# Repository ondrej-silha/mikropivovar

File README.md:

Mikropivovar
=
Homemade microbrewery control system with the possibility of controlling the cellar and the pump.
Powered by Atmega328PU

Futures
-
* 4 relay output (3x AC 230, 1x DC 12V)
* 2 temperature input
* Graphic color touchable display
* Beeper

Used software
- 
* Kicad
* Freecad
* Arduino ide
* Nextion editor

Board preview
-

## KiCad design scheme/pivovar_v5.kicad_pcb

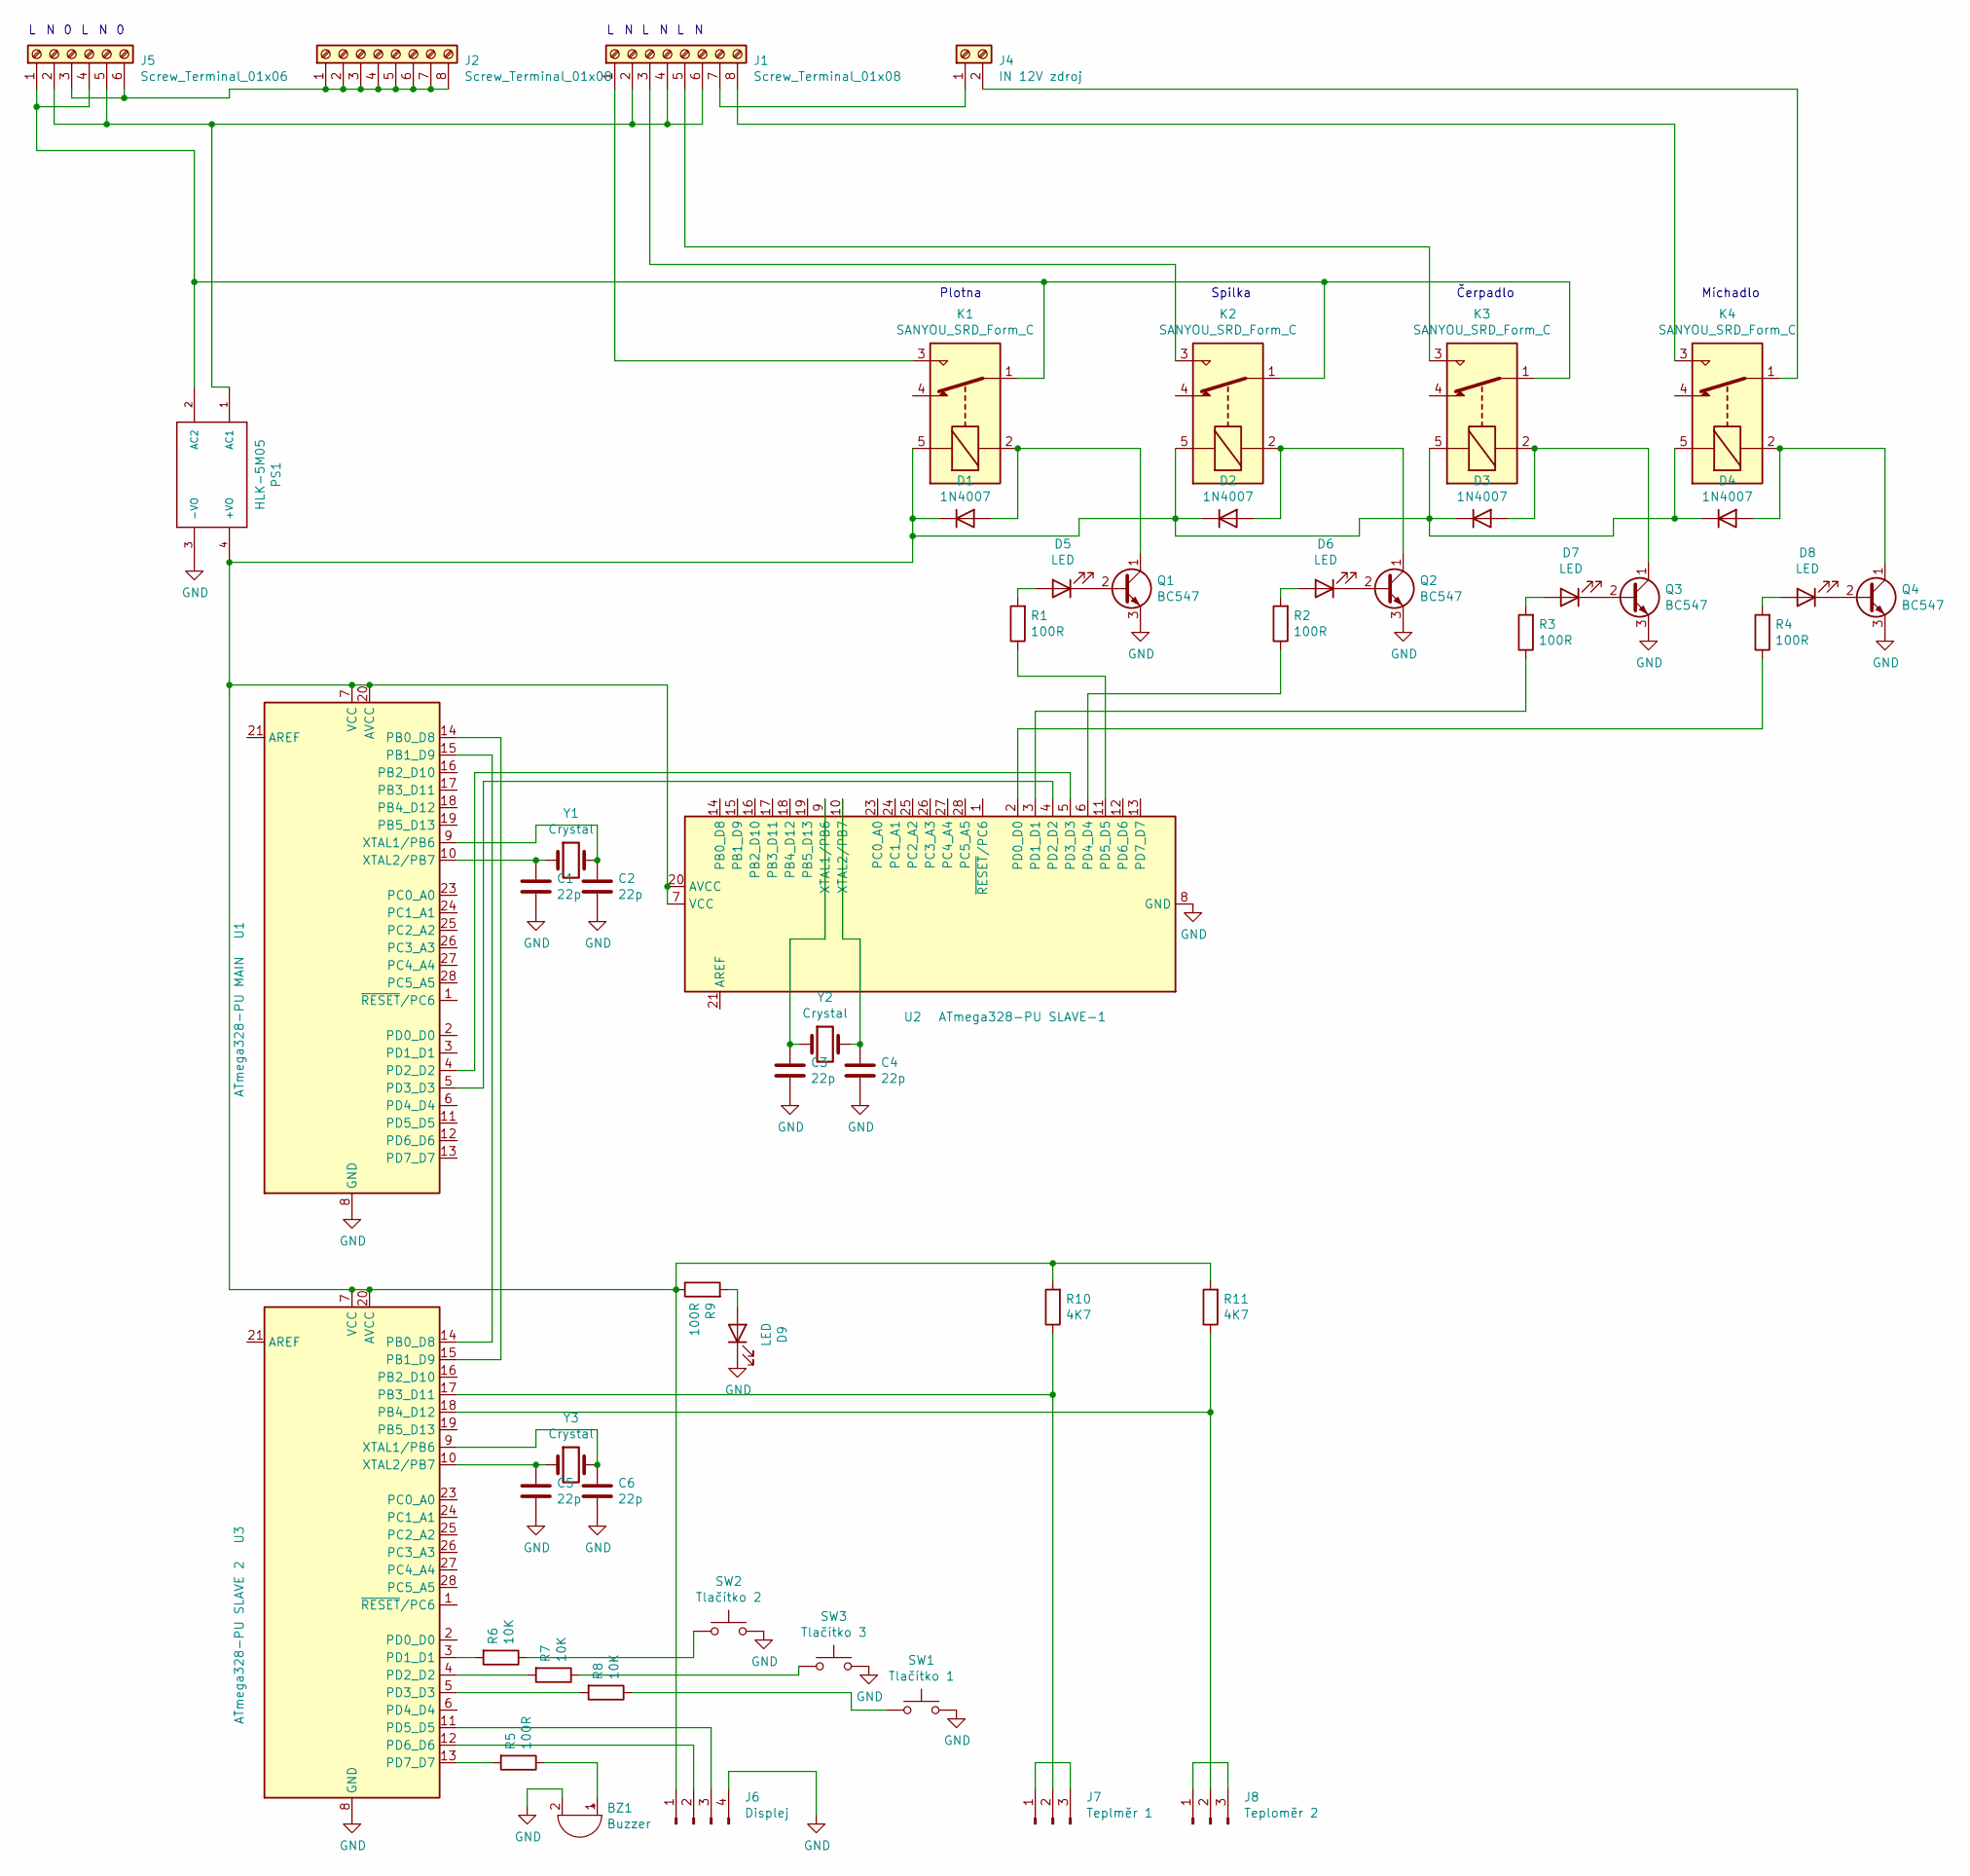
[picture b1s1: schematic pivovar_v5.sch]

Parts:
BZ1: Buzzer; JST_EH_B2B-EH-A_1x02_P2.50mm_Vertical
C1, C2, C3, C4, C5, C6: 22p; C_Disc_D6.0mm_W4.4mm_P5.00mm
D1, D2, D3, D4: 1N4007; D_DO-15_P12.70mm_Horizontal
D5, D6, D7, D8, D9: LED; JST_EH_B2B-EH-A_1x02_P2.50mm_Vertical
J1, J2: Screw_Terminal_01x08; TerminalBlock_Phoenix_MKDS-1,5-8-5.08_1x08_P5.08mm_Horizont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
J4: IN 12V zdroj; TerminalBlock_Phoenix_MKDS-1,5-2-5.08_1x02_P5.08mm_Horizont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
J5: Screw_Terminal_01x06; TerminalBlock_Phoenix_MKDS-1,5-6-5.08_1x06_P5.08mm_Horizont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
J6: Displej; JST_EH_B4B-EH-A_1x04_P2.50mm_Vertical
J7: Teplměr 1; JST_EH_B3B-EH-A_1x03_P2.50mm_Vertical
J8: Teploměr 2; JST_EH_B3B-EH-A_1x03_P2.50mm_Vertical
K1, K2, K3, K4: SANYOU_SRD_Form_C; Relay_SPDT_SANYOU_SRD_Series_Form_C
PS1: HLK-5M05; CONV_HLK-5M05
Q1, Q2, Q3, Q4: BC547; TO-92_Inline_Wide
R1, R2, R3, R4, R5, R9: 100R; R_Axial_DIN0309_L9.0mm_D3.2mm_P12.70mm_Horizontal
R6, R7, R8: 10K; R_Axial_DIN0309_L9.0mm_D3.2mm_P12.70mm_Horizontal
R10, R11: 4K7; R_Axial_DIN0309_L9.0mm_D3.2mm_P12.70mm_Horizontal
SW1: Tlačítko 1; JST_EH_B2B-EH-A_1x02_P2.50mm_Vertical
SW2: Tlačítko 2; JST_EH_B2B-EH-A_1x02_P2.50mm_Vertical
SW3: Tlačítko 3; JST_EH_B2B-EH-A_1x02_P2.50mm_Vertical
U1: ATmega328-PU MAIN; DIP-28_W7.62mm
U2: ATmega328-PU SLAVE-1; DIP-28_W7.62mm
U3: ATmega328-PU SLAVE 2; DIP-28_W7.62mm
Y1, Y2, Y3: Crystal; Crystal_HC49-4H_Vertical

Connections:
GND: BZ1.2 (+), C1.2, C2.2, C3.2, C4.2, C5.2, C6.2, D9.1 (K), J6.4, PS1.3 (-VO), Q1.3 (E), Q2.3 (E), Q3.3 (E), Q4.3 (E), SW1.2, SW2.2, SW3.2, U1.8 (GND), U1.22 (GND), U2.8 (GND), U2.22 (GND), U3.8 (GND), U3.22 (GND); also elsewhere on the board
unnamed: BZ1.1 (-), R5.1
unnamed 2: C1.1, U1.10 (XTAL2/PB7), Y1.1; also elsewhere on the board
unnamed 3: C2.1, U1.9 (XTAL1/PB6), Y1.2; also elsewhere on the board
unnamed 4: C3.1, U2.9 (XTAL1/PB6), Y2.1; also elsewhere on the board
unnamed 5: C4.1, U2.10 (XTAL2/PB7), Y2.2; also elsewhere on the board
unnamed 6: C5.1, U3.10 (XTAL2/PB7), Y3.1; also elsewhere on the board
unnamed 7: C6.1, U3.9 (XTAL1/PB6), Y3.2; also elsewhere on the board
unnamed 8: D1.1 (K), D2.1 (K), D3.1 (K), D4.1 (K), J6.1, K1.5, K2.5, K3.5, K4.5, PS1.4 (+VO), R9.1, R10.2, R11.2, U1.7 (VCC), U1.20 (AVCC), U2.7 (VCC), U2.20 (AVCC), U3.7 (VCC), U3.20 (AVCC); also elsewhere on the board
unnamed: D1.2 (A), K1.2, Q1.1 (C)
unnamed: D2.2 (A), K2.2, Q2.1 (C)
unnamed: D3.2 (A), K3.2, Q3.1 (C)
unnamed: D4.2 (A), K4.2, Q4.1 (C)
unnamed: D5.1 (K), Q1.2 (B)
unnamed: D5.2 (A), R1.2
unnamed: D6.1 (K), Q2.2 (B)
unnamed: D6.2 (A), R2.2
unnamed: D7.1 (K), Q3.2 (B)
unnamed: D7.2 (A), R3.2
unnamed: D8.1 (K), Q4.2 (B)
unnamed: D8.2 (A), R4.2
unnamed: D9.2 (A), R9.2
unnamed: J1.1, K1.3
unnamed: J1.2, J1.4, J1.6, J5.2, J5.5, PS1.1 (AC1)
unnamed: J1.3, K2.3
unnamed: J1.5, K3.3
unnamed: J1.7, J4.1
unnamed: J1.8, K4.3
unnamed: J2.1, J2.2, J2.3, J2.4, J2.5, J2.6, J2.7, J2.8, J5.3, J5.6
unnamed: J4.2, K4.1
unnamed: J5.1, J5.4, K1.1, K2.1, K3.1, PS1.2 (AC2)
unnamed 31: J6.2, U3.12 (PD6_D6); also elsewhere on the board
unnamed 32: J6.3, U3.11 (PD5_D5); also elsewhere on the board
unnamed: J7.1, J7.3
unnamed 34: J7.2, R10.1, U3.17 (PB3_D11); also elsewhere on the board
unnamed: J8.1, J8.3
unnamed 36: J8.2, R11.1, U3.18 (PB4_D12); also elsewhere on the board
unnamed 41: R1.1, U2.11 (PD5_D5); also elsewhere on the board
unnamed 42: R2.1, U2.6 (PD4_D4); also elsewhere on the board
unnamed 43: R3.1, U2.3 (PD1_D1); also elsewhere on the board
unnamed 44: R4.1, U2.2 (PD0_D0); also elsewhere on the board
unnamed 45: R5.2, U3.13 (PD7_D7); also elsewhere on the board
unnamed: R6.1, SW2.1
unnamed 47: R6.2, U3.3 (PD1_D1); also elsewhere on the board
unnamed: R7.1, SW3.1
unnamed 49: R7.2, U3.4 (PD2_D2); also elsewhere on the board
unnamed: R8.1, SW1.1
unnamed 51: R8.2, U3.5 (PD3_D3); also elsewhere on the board
unnamed 55: U1.4 (PD2_D2), U2.5 (PD3_D3); also elsewhere on the board
unnamed 56: U1.5 (PD3_D3), U2.4 (PD2_D2); also elsewhere on the board
unnamed 61: U1.14 (PB0_D8), U3.15 (PB1_D9); also elsewhere on the board
unnamed 62: U1.15 (PB1_D9), U3.14 (PB0_D8); also elsewhere on the board

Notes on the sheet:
Plotna
Spilka
Čerpadlo
Míchadlo

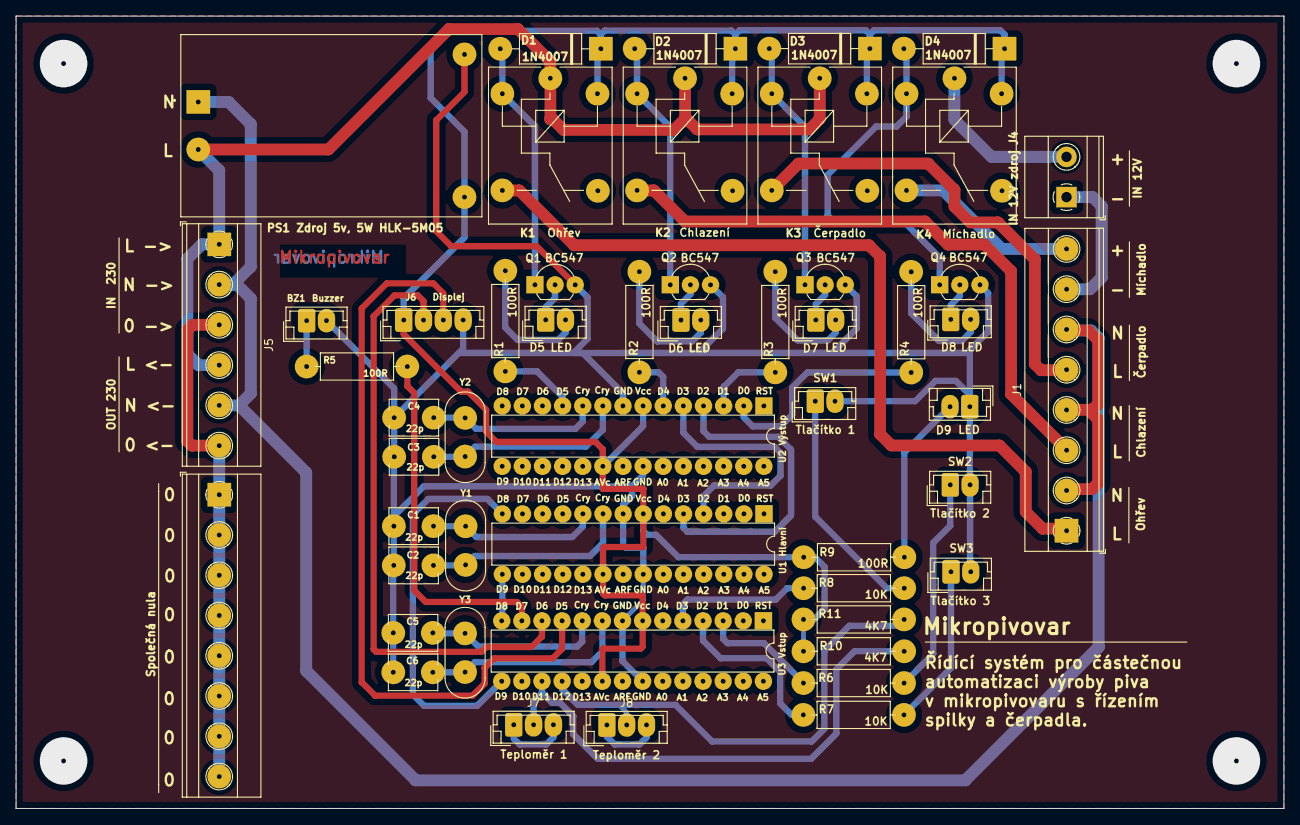
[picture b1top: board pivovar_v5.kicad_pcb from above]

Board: 2 copper layers, 160.0 x 100.0 mm, 52 parts (0 on the bottom side), 52 nets.

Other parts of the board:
U1 Hlavní: ATmega328-PU MAIN; DIP-28_W7.62mm
U2 Výstup: ATmega328-PU SLAVE-1; DIP-28_W7.62mm
U3 Vstup: ATmega328-PU SLAVE 2; DIP-28_W7.62mm

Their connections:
GND: U1 Hlavní.8, U1 Hlavní.22, U2 Výstup.8, U2 Výstup.22, U3 Vstup.8, U3 Vstup.22; also elsewhere on the board
unnamed 2: U1 Hlavní.10; also elsewhere on the board
unnamed 3: U1 Hlavní.9; also elsewhere on the board
unnamed 4: U2 Výstup.9; also elsewhere on the board
unnamed 5: U2 Výstup.10; also elsewhere on the board
unnamed 6: U3 Vstup.10; also elsewhere on the board
unnamed 7: U3 Vstup.9; also elsewhere on the board
unnamed 8: U1 Hlavní.7, U1 Hlavní.20, U2 Výstup.7, U2 Výstup.20, U3 Vstup.7, U3 Vstup.20; also elsewhere on the board
unnamed 31: U3 Vstup.12; also elsewhere on the board
unnamed 32: U3 Vstup.11; also elsewhere on the board
unnamed 34: U3 Vstup.17; also elsewhere on the board
unnamed 36: U3 Vstup.18; also elsewhere on the board
unnamed 41: U2 Výstup.11; also elsewhere on the board
unnamed 42: U2 Výstup.6; also elsewhere on the board
unnamed 43: U2 Výstup.3; also elsewhere on the board
unnamed 44: U2 Výstup.2; also elsewhere on the board
unnamed 45: U3 Vstup.13; also elsewhere on the board
unnamed 47: U3 Vstup.3; also elsewhere on the board
unnamed 49: U3 Vstup.4; also elsewhere on the board
unnamed 51: U3 Vstup.5; also elsewhere on the board
unnamed 55: U1 Hlavní.4, U2 Výstup.5; also elsewhere on the board
unnamed 56: U1 Hlavní.5, U2 Výstup.4; also elsewhere on the board
unnamed 61: U1 Hlavní.14, U3 Vstup.15; also elsewhere on the board
unnamed 62: U1 Hlavní.15, U3 Vstup.14; also elsewhere on the board

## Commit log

2020-09-16 Scheme + PCB
2020-09-16 PCB screen
2020-09-16 Add readme
